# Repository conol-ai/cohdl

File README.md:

# CoHDL

CoHDL is the programming language that makes schematic (PCB) design AI-native — the way software became AI-native. AI generates and repairs hardware; the compiler is the oracle that grades it.

This is the **v2 ground-up implementation**, restarted 2026-07-13 from the redesigned language specification. The central thesis of the redesign: **strictness buys expressiveness** — push correctness into the type system wherever a mistake is structural (wrong units, unresolved pins, unsatisfied trait bounds), and reserve DRC only for genuinely emergent, whole-graph checks (net voltage, driver conflicts).

The previous implementation lives on the [`legacy`](https://github.com/conol-ai/cohdl/tree/legacy) branch. It is not being fixed; this is a fresh build informed by its lessons.

## Design repository

The source of truth for the language design is the Coherent Design Repository on conol.ai:
<https://conol.ai/share/note/tqrnb5h4l0dv8c14dkd17h4l>

A snapshot (taken 2026-07-13) is committed under [`docs/design/`](docs/design/). Key documents:

- [MVP Definition](docs/design/09-mvp-definition.md) — the scope line, demo scenario, and exit criteria this repository was built toward
- [Language Specification](docs/design/10-language-specification.md) — the compiled statement of what the language is (Accepted RFCs only)
- RFC-001…RFC-007 — the seven Accepted P0 RFCs: units-as-types, pin connection-obligation typing, trait satisfaction at impl time, DRC/type-system reclassification, collision-free designator allocation, nested fn call semantics, generics-over-specs
- RFC-008…RFC-018 — the post-MVP Accepted RFCs (compiler-implemented, with named open gaps recorded in [`docs/compliance-report.md`](docs/compliance-report.md) — notably RFC-016/017 on-disk dependency loading is not yet built, and RFC-014/015 real-client/partner acceptance passes remain open): structural variants, `cohdl fmt`, `cohdl check --json`, the formal error-code registry, `#[intent]` annotations, layout constraints, the LSP server (`cohdl lsp`, [`docs/lsp.md`](docs/lsp.md)), the IPC-2581 handoff document (`build --emit ipc2581`, [`docs/ipc2581.md`](docs/ipc2581.md)), the module system, the library registry, the pad/footprint format (`pad`/`footprint` geometry → `.kicad_mod` + IPC-2581 pins), and a real VS Code extension (`editors/vscode/`, packaging `cohdl lsp` with a TextMate grammar — RFC-019)

## MVP (v0.1) scope

The smallest slice of the spec that proves the thesis end-to-end:

1. **Parser** — traits, devices, free-standing `impl`, `fn` declarations/calls (nested), design bodies (`inst`, `net`, `nc`), the eleven unit-type literal forms
2. **Type checker** (the heart) — zero-coercion unit types, pin connection-obligation exhaustiveness, trait satisfaction with explicit mapping, generic resolution with trait-bound checking, nested fn expansion with cycle detection
3. **Residual DRC** — exactly four rules: voltage-exceed, polarity-mismatch, single-driver, multi-driver
4. **Designators** — collision-free allocator, `design.lock` with tombstones, `#[designator("…")]` overrides
5. **Codegen** — KiCad `.net` netlist + BOM CSV
6. **Minimal std library** — only the universal traits every component package needs
7. **Repair harness** — generate → check → repair loop driving an LLM against the compiler's diagnostics

The proof: an AI writes a board from a plain-language spec, the type checker catches its structural mistakes as precise compile errors, the AI repairs them from those diagnostics, and the result is a real, importable KiCad netlist with an honest BOM.

## Status

All MVP exit criteria are met, and all nineteen Accepted RFC areas (RFC-001…019) have implementation work with conformance suites. That is deliberately not a claim of full accepted-text compliance: requirements that are incomplete (e.g. RFC-014's real-editor acceptance pass and RFC-015's real-partner/Quilter import pass — both open), deliberately deviating (e.g. the E9xx code assignment, D003's role-aware reading, RFC-015's constraint mapping riding vendor extensions rather than native IPC semantics), or unrepresentable pending note-side amendments (e.g. RFC-013's E1005) are each recorded with rationale in the ledger, [`docs/compliance-report.md`](docs/compliance-report.md). Tested (`cargo test` — [`tests/exit_criteria.rs`](tests/exit_criteria.rs) maps 1:1 to the MVP checklist; each post-MVP RFC has its own conformance suite under `tests/`). The demo loop has run end-to-end: see [`docs/demo/`](docs/demo/) for transcripts (including a genuine E701 unresolved-required-pin catch + repair) and the emitted netlist/BOM. RFC/decision-record accuracy was audited claim-by-claim: [`docs/compliance-report.md`](docs/compliance-report.md). The KiCad checkpoint has been executed with real KiCad (pcbnew imported the netlist, resolved all footprints and pads; board + render in `docs/demo/`).

## Install

One line (macOS and Linux; installs to `~/.cohdl/bin`):

```sh
curl -fsSL https://raw.githubusercontent.com/conol-ai/cohdl/main/install.sh | sh
```

Prebuilt binaries (and their `sha256sums.txt`) are attached to every
[`vX.Y.Z` release](https://github.com/conol-ai/cohdl/releases); Windows users
download `cohdl-vX.Y.Z-x86_64-pc-windows-msvc.tar.gz` by hand. An installed
binary updates itself with `cohdl self-update` (`--check` reports without
installing). Building from source stays `cargo build` (toolchain pinned by
`rust-toolchain.toml`).

## Using it

```sh
cargo run -- check examples/sf32-miniboard       # SF32 miniboard: SiFli BLE eval board
cargo run -- build examples/rpi-pico2            # + designators, parts, KiCad .net + BOM CSV
cargo run -- check examples/rpi-pico2 --json     # structured diagnostics (RFC-010)
cargo run -- build examples/rpi-pico2 --emit ipc2581  # + IPC-2581 handoff document (RFC-015)
cargo run -- build examples/rpi-pico2 --emit kicad_pcb # + a native KiCad 10 board file — no KiCad needed
cargo run -- build examples/rpi-pico2 --emit easyeda   # + an EasyEDA / LCEDA Pro netlist (.enet)
cargo run -- build examples/rpi-pico2 --supplier acme   # + supplier BOM/map/CPL (RFC-034)
cargo run -- fmt lib --check                     # canonical-form gate (RFC-009)
cargo run -- lsp                                 # LSP server on stdio (RFC-014, docs/lsp.md)
cargo run -- search TPS59650                     # search registry packages + public parts
cargo run -- search TPS59650 --json              # the same bounded results as JSON
python3 harness/repair_loop.py                   # the generate → check → repair demo
```

Physical builds of placed designs also write `out/<name>-cpl.csv`, the
supplier-neutral five-column placement CSV. Under RFC-034,
repeatable `--supplier ID` selects each instance's own primary or eligible
alternate binding and writes `out/<name>-<ID>-bom.csv`,
`out/<name>-<ID>-map.json`, and (for physical builds)
`out/<name>-<ID>-cpl.csv`. The map preserves the selected entry identity and
placement transform; `tools/smt_pos.py --map` can apply it to the emitted
KiCad board. `--logical-only` remains a logical-artifact boundary: it emits
no neutral or supplier CPL, even when `--supplier` is present. Supplier BOM
and map remain available in that mode. Repeatable build option
`--bottom-rotation ID=VALUE` selects the bottom-side angle convention (`kicad`
or `mirrored`) for a supplier CPL; IDs must also be selected by `--supplier`
and default to `kicad`. Schema-2 maps record the convention actually used,
including in logical-only builds, and `tools/smt_pos.py --map` applies the same
rule (schema-1 maps retain `kicad` compatibility).

`cohdl search QUERY [--json]` is read-only discovery: it needs no project and
no registry login. Queries are trimmed, must contain at least three Unicode
scalar values, may be at most 128 UTF-8 bytes, and may not contain control
characters. Results identify the owning package and exact most-recently-
published version as well as importable public part paths and matching primary
or alternate manufacturer/MPN data; a valid query with no matches still exits
successfully. Use the standard option terminator when a literal query starts
with a hyphen, for example `cohdl search -- -12V`. “Most recently published”
is publication chronology, not the greatest semantic version chosen by an
unversioned `cohdl add`/`cohdl update`.
The package and part result families are bounded independently; each exposes
`has_more` when truncated and never a total count. Human output separates the
two families, while `--json` returns the same rows as one discovery document.
For rollout, owners of existing packages backfill the current searchable
version once with `cohdl docs --publish`; this does not change its tar or hash.

`std` is a core-traits-only prelude; it carries no devices, parts, pads, or
footprints. Shipped component packages include `passive`, `connectors`, `usb`,
`esd`, `diode`, `flash`, `ldo`, `led`, `mic`, `mosfet`, `osc`, and
manufacturer packages for Espressif, Raspberry Pi, Richtek, ST, and TI.
Projects pin every package they use to an exact version under
`[dependencies]`; see [`lib/README.md`](lib/README.md) for the complete
namespace map.

Two reference designs live in `examples/`: Raspberry Pi **Pico 2** and the
**SF32 miniboard**. (The **OpenMicro** macropad — the wired STM32F072 v1 and
its wireless SF32LB52 successor v2 — graduated to its own repository,
`openmicrokbd`, which carries the whole product: hardware source, firmware,
host app, and fab releases under `hw/v1/` and `hw/v2/`.)

An **AI voice robot-dog mainboard** is in progress and not yet in the tree; its
exit-criteria test is checked in but ignored until the example lands. It
combines an ESP32-S3-N8R2, stereo I2S microphones,
isolated speaker playback, a translated 1.8 V IMU domain, USB-C, a protected
default-off 7 A actuator rail, and eight 5 V servo PWM channels. Keyed 4/6-pin
Micro-Fit harnesses prevent the BEC input from being interchanged with a leg.

### Build artifacts

`cohdl build` writes to `out/` (or `--out-dir`): the KiCad netlist (`<name>.net`), the BOM (`<name>-bom.csv`), the designator lock (`design.lock` in the project root), a `.kicad_mod` per pad-bearing footprint under `out/footprints/` (RFC-018), and — only when the design declares layout metadata — the layout-constraint artifact `<name>-layout.json` (schema: [`docs/layout-json.md`](docs/layout-json.md)). With `--emit ipc2581` it additionally writes the IPC-2581B1 handoff document `<name>.xml` (RFC-015; [`docs/ipc2581.md`](docs/ipc2581.md)), with `--emit kicad_pcb` a native KiCad 10 board file `<name>.kicad_pcb` — placements, net-bound footprints, and the board outline, with no KiCad installation involved ([`docs/kicad_pcb.md`](docs/kicad_pcb.md)), and with `--emit easyeda` an EasyEDA / LCEDA Pro netlist `<name>.enet` for **File → Import → Netlist** ([`docs/easyeda.md`](docs/easyeda.md)); the flags compose. Stale layout/IPC/board artifacts are removed when their source data is gone (the IPC document only if CoHDL wrote it — its completeness marker establishes ownership).

### Looking at a design

A checked design can be read back as an interactive schematic-style board —
every instance, net and pin the compiler resolved, searchable and traceable,
with datasheets and to-scale footprint previews in a side panel. It is a
read-only projection: the `.cohdl` source stays the only thing that defines
the circuit.

On macOS, download the signed, notarized app from the latest
[`explorer-v*` release](https://github.com/conol-ai/cohdl/releases?q=explorer&expanded=true)
(mount the DMG, drag to Applications, pick a project). Or run it from source:

```sh
cd explorer/web && npm install && npm run build   # once
cd ../extractor
COHDL_LIB=../../lib cargo run --release -- ../../examples/rpi-pico2 \
    --serve --dist ../web/dist --port 5199        # http://127.0.0.1:5199/
```

Editing any source file re-extracts and refreshes the page within ~500 ms; a
source that fails to compile keeps the last good view and shows the
diagnostics. Extraction, layout and wire routing are deterministic code — the
same source always draws the same board. An agent's only input is the
partition file `explorer/views/<Design>.view.json`, which names the page tabs
and the region each part belongs to; the contract for writing one is
[`explorer/skills/view-gen/SKILL.md`](explorer/skills/view-gen/SKILL.md).
See [`explorer/README.md`](explorer/README.md).

### Exit codes

`0` = clean (warnings and a valid no-match search are allowed); `1` = the
accepted command failed (source errors, non-canonical `fmt --check`, or an E1204
search registry/protocol failure); `2` = invocation-level failure (bad flags,
an invalid search query, missing project, design selection, nothing to build);
`3` = `cohdl suppliers` found an `unknown` or `mismatched` audited binding
(out-of-stock, unbound, and unlisted suppliers do not change the exit code).
Human diagnostics use stderr. A successful `search --json` emits its discovery
document on stdout, and an E1204 failure in that mode emits the existing
diagnostic JSON there; bad invocations remain prose-only on stderr. See the
formal [`docs/error-codes.md`](docs/error-codes.md) registry. Note: RFC-010's
text reserves stderr prose for pre-collection failures, so classifying
post-collection selection failures this way is a documented deviation pending
a note-side amendment (or a v2 schema envelope).

## License

MIT — see [`LICENSE`](LICENSE). This covers the compiler crate, the libraries
under `lib/`, the reference designs in `examples/`, the registry
server in `registry/`, the VS Code extension in `editors/vscode/`, and the
tooling in `tools/` and `harness/`.

Third-party material is not covered by that grant: the manufacturer documents
under `lib/*/docs/` keep their owners' terms, KiCad-derived footprints are
CC-BY-SA-4.0 as each such package records in its manifest and license files, and the supplier
catalog facts and assembly-preview captures under `tools/sourcing_data/` are
described in [`tools/sourcing_data/NOTICE.md`](tools/sourcing_data/NOTICE.md).

Every package published to registry.cohdl.org must declare its own
`[package] license`; every package shipped under `lib/` declares `MIT`.

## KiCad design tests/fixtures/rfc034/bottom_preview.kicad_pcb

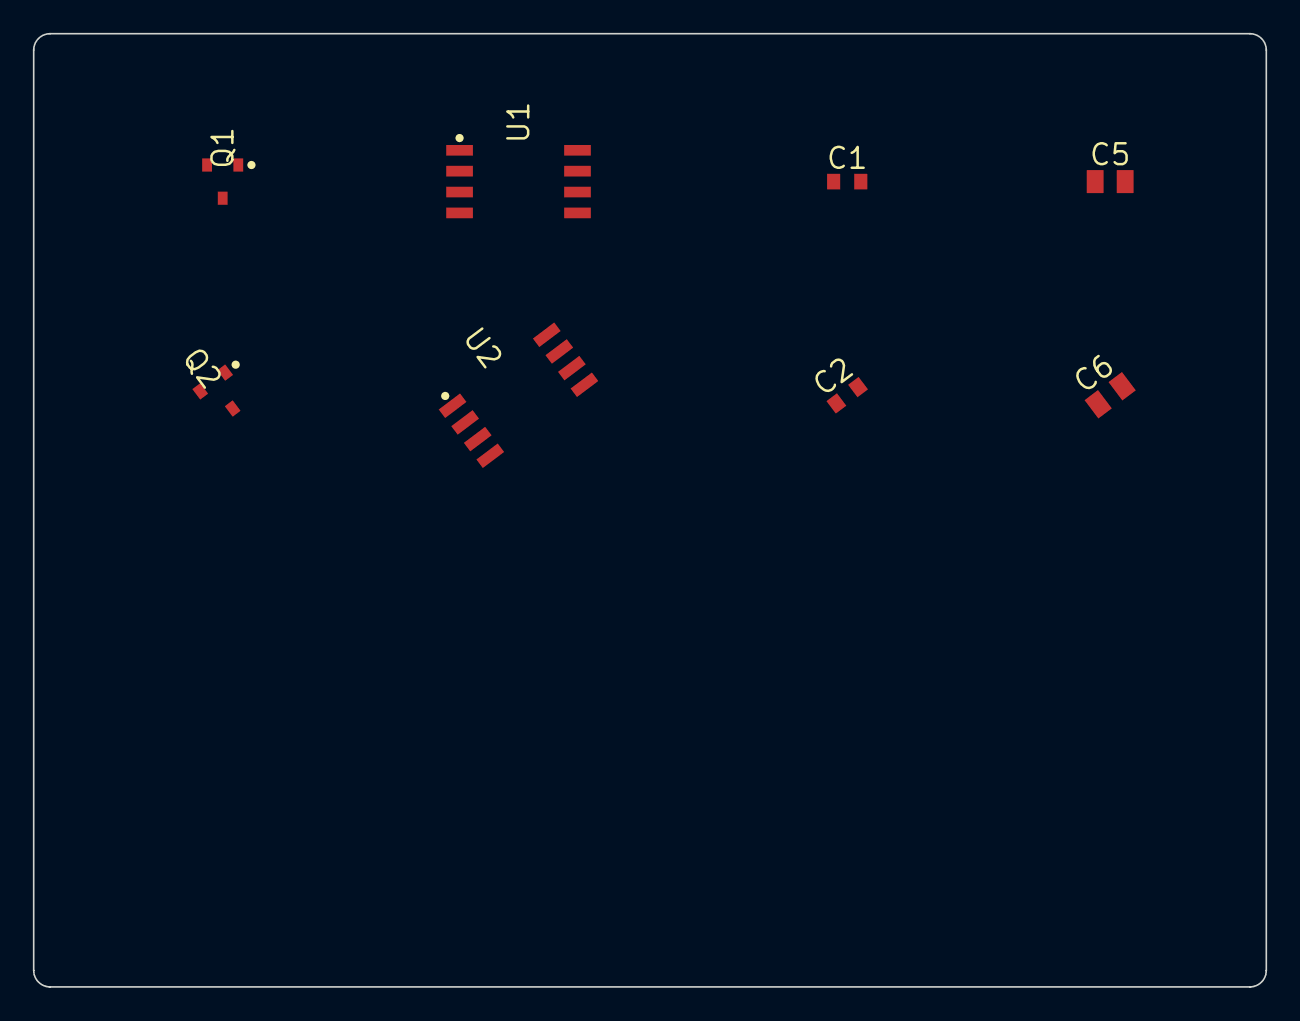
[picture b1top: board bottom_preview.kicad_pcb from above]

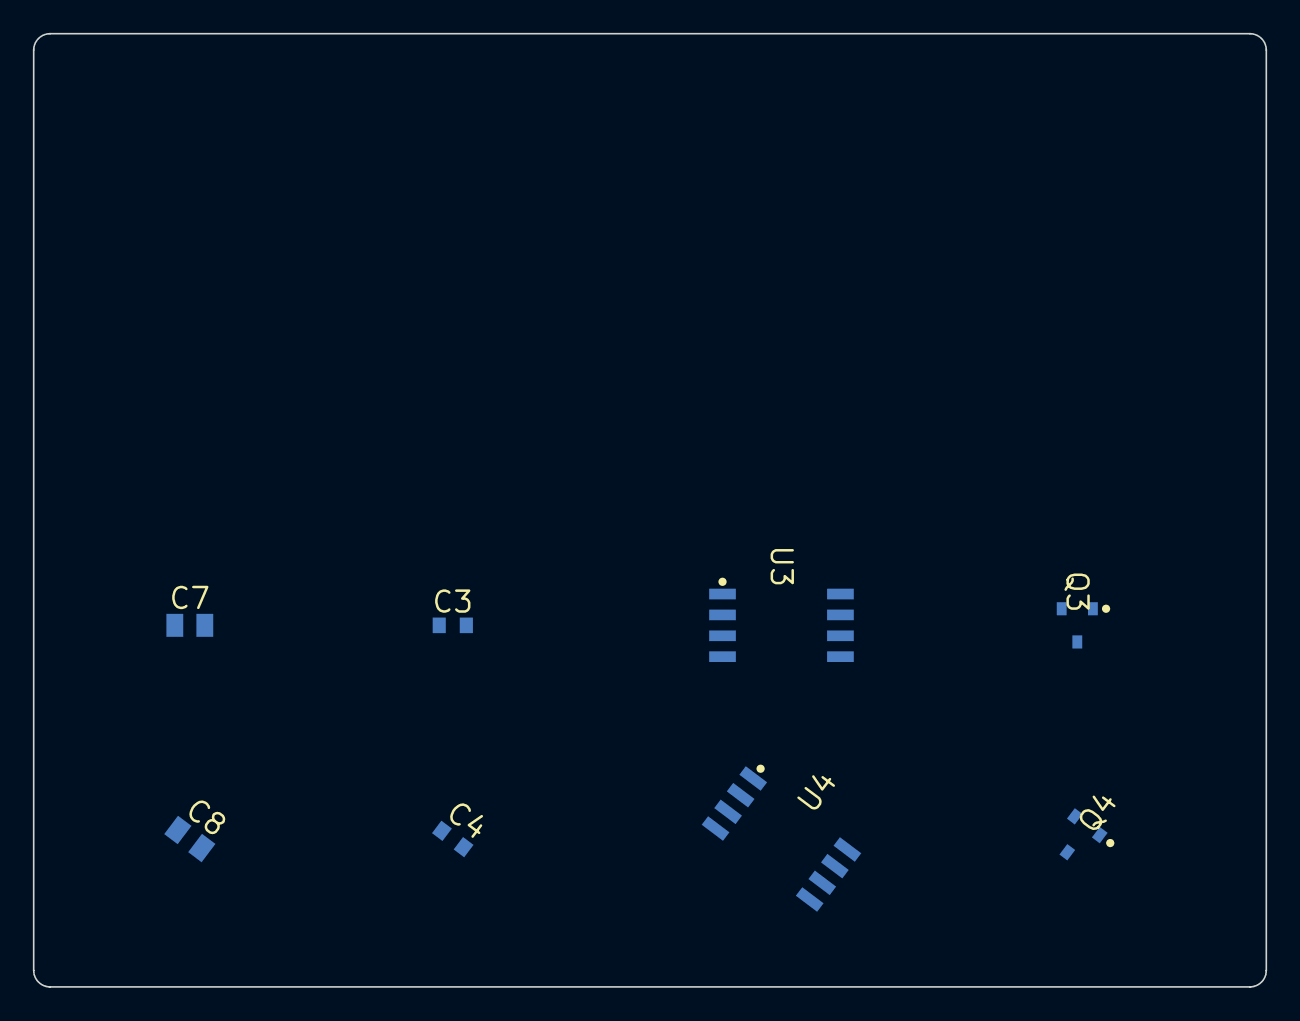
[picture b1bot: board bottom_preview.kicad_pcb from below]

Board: 2 copper layers, 75.0 x 58.0 mm, 16 parts (8 on the bottom side), 2 nets, no tracks yet.

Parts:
C1, C2, C3, C4: 27pF; passive-CHIP_0603
C5, C6, C7, C8: 15pF; passive-CHIP_0805
Q1, Q2, Q3, Q4: NPN_SOT23_BEC; transistor-FP_JSCJ_SOT23
U1, U2, U3, U4: W25Q128JV; soic-SOIC8P127X790X216N

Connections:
GND: C1.2, C2.2, C3.2, C4.2, C5.2, C6.2, C7.2, C8.2, Q1.2, Q2.2, Q3.2, Q4.2, U1.4, U2.4, U3.4, U4.4
V3V3: C1.1, C2.1, C3.1, C4.1, C5.1, C6.1, C7.1, C8.1, Q1.1, Q1.3, Q2.1, Q2.3, Q3.1, Q3.3, Q4.1, Q4.3, U1.8, U2.8, U3.8, U4.8

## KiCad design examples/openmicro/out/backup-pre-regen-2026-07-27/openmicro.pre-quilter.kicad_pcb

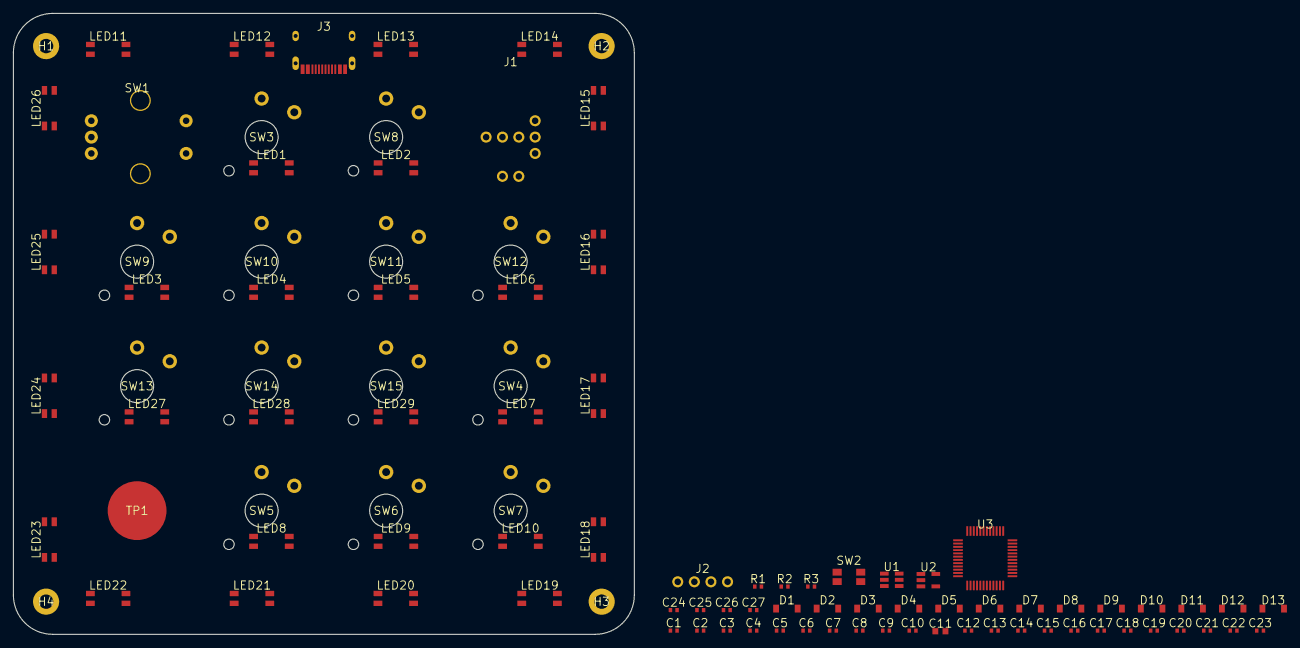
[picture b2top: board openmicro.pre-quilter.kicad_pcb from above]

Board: 2 copper layers, 95.0 x 95.0 mm, 98 parts (0 on the bottom side), 70 nets, no tracks yet.

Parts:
C1, C2, C3, C4, C5, C6, C7, C8, C9, C10, C13, C14, C15, C16, C17, C18, C19, C20, C21, C22, C23, C24, C25, C26, C27: 100nF; std-CHIP_0402
C11: 4.7uF; std-CHIP_0603
C12: 1uF; std-CHIP_0402
D1, D2, D3, D4, D5, D6, D7, D8, D9, D10, D11, D12, D13: Diode_1N4148; openmicro-FP_D_SOD_123
H1, H2, H3, H4: MountingHole; openmicro-FP_MountingHole_M2
J1: ThumbPointer; openmicro-FP_Joystick_RKJXV
J2: SWD_Header; openmicro-FP_Header_1x4
J3: USB_C_Receptacle_2_0; std-FP_USB_C_Receptacle_HRO_TYPE_C_31_M_12
LED1, LED2, LED3, LED4, LED5, LED6, LED7, LED8, LED9, LED10, LED11, LED12, LED13, LED14, LED15, LED16, LED17, LED18, LED19, LED20, LED21, LED22, LED23, LED24, LED25, LED26, LED27, LED28, LED29: SK6812; openmicro-FP_LED_SK6812MINI_E
R1: 10kohm; std-CHIP_0402
R2, R3: 5.1kohm; std-CHIP_0402
SW1: RotaryEC11; openmicro-FP_Encoder_EC11
SW2: ResetSwitch; openmicro-FP_SW_Reset
SW3, SW4, SW5, SW6, SW7, SW8, SW9, SW10, SW11, SW12, SW13, SW14, SW15: KeySwitch; openmicro-FP_SW_Choc_V2
TP1: CapTouchPad; openmicro-FP_TouchPad
U1: USBLC6; openmicro-FP_SOT_23_6
U2: AP2112K_3V3; std-SOT5P95X290X160N
U3: STM32F072CBT6; openmicro-QFP50P900X900X160_48N

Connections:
BOOT0: R1.1, U3.44
CC1: J3.A5, R2.1
CC2: J3.B5, R3.1
COL0: D1.1, D5.1, D9.1, D13.1, U3.25
COL1: D2.1, D6.1, D10.1, U3.26
COL2: D3.1, D7.1, D11.1, U3.27
COL3: D4.1, D8.1, D12.1, U3.28
ENC_A: SW1.1, U3.29
ENC_B: SW1.3, U3.30
ENC_SW: SW1.4, U3.31
GND: C1.2, C2.2, C3.2, C4.2, C5.2, C6.2, C7.2, C8.2, C9.2, C10.2, C11.2, C12.2, C13.2, C14.2, C15.2, C16.2, C17.2, C18.2, C19.2, C20.2, C21.2, C22.2, C23.2, C24.2, C25.2, C26.2, C27.2, H1.1, H2.1, H3.1, H4.1, J1.1, J1.4, J1.8, J2.3, J3.A1, J3.A12, J3.B1, J3.B12, J3.SH1, J3.SH2, J3.SH3, J3.SH4, LED1.3, LED2.3, LED3.3, LED4.3, LED5.3, LED6.3, LED7.3, LED8.3, LED9.3, LED10.3, LED11.3, LED12.3, LED13.3, LED14.3, LED15.3, LED16.3, LED17.3, LED18.3, LED19.3, LED20.3, LED21.3, LED22.3, LED23.3, LED24.3, LED25.3, LED26.3, LED27.3, LED28.3, LED29.3, R1.2, R2.2, R3.2, SW1.2, SW1.5, SW1.6, SW1.7, SW2.3, SW2.4, U1.2, U2.2, U3.8, U3.23, U3.35, U3.47
JOY_SW: J1.7, U3.12
JOY_X: J1.2, U3.10
JOY_Y: J1.5, U3.11
KEY1: D1.2, SW3.2
KEY2: D6.2, SW8.2
KEY3: D7.2, SW9.2
KEY4: D8.2, SW10.2
KEY5: D9.2, SW11.2
KEY6: D10.2, SW12.2
KEY7: D11.2, SW13.2
KEY8: D12.2, SW14.2
KEY9: D13.2, SW15.2
KEY10: D2.2, SW4.2
KEY11: D3.2, SW5.2
KEY12: D4.2, SW6.2
KEY13: D5.2, SW7.2
LED_D0: LED1.4, U3.41
LED_D1: LED1.2, LED2.4
LED_D2: LED2.2, LED3.4
LED_D3: LED3.2, LED4.4
LED_D4: LED4.2, LED5.4
LED_D5: LED5.2, LED6.4
LED_D6: LED6.2, LED27.4
LED_D7: LED27.2, LED28.4
LED_D8: LED28.2, LED29.4
LED_D9: LED7.4, LED29.2
LED_D10: LED7.2, LED8.4
LED_D11: LED8.2, LED9.4
LED_D12: LED9.2, LED10.4
NRST: SW2.1, SW2.2, U3.7
ROW0: SW3.1, SW8.1, SW9.1, SW10.1, U3.18
ROW1: SW11.1, SW12.1, SW13.1, SW14.1, U3.19
ROW2: SW4.1, SW5.1, SW6.1, SW15.1, U3.20
ROW3: SW7.1, U3.21
SWCLK: J2.2, U3.37
SWDIO: J2.1, U3.34
TOUCH: TP1.1, U3.13
UG_D0: LED11.4, U3.40
UG_D1: LED11.2, LED12.4
UG_D2: LED12.2, LED13.4
UG_D3: LED13.2, LED14.4
UG_D4: LED14.2, LED15.4
UG_D5: LED15.2, LED16.4
UG_D6: LED16.2, LED17.4
UG_D7: LED17.2, LED18.4
UG_D8: LED18.2, LED19.4
UG_D9: LED19.2, LED20.4
UG_D10: LED20.2, LED21.4
UG_D11: LED21.2, LED22.4
UG_D12: LED22.2, LED23.4
UG_D13: LED23.2, LED24.4
UG_D14: LED24.2, LED25.4
UG_D15: LED25.2, LED26.4
USBC_DM: J3.A7, J3.B7, U1.3
USBC_DP: J3.A6, J3.B6, U1.1
USB_DM: U1.4, U3.32
USB_DP: U1.6, U3.33
V3V3: C1.1, C2.1, C3.1, C12.1, J1.3, J1.6, J2.4, U2.5, U3.1, U3.9, U3.24, U3.36, U3.48
VBUS: C4.1, C5.1, C6.1, C7.1, C8.1, C9.1, C10.1, C11.1, C13.1, C14.1, C15.1, C16.1, C17.1, C18.1, C19.1, C20.1, C21.1, C22.1, C23.1, C24.1, C25.1, C26.1, C27.1, J3.A4, J3.A9, J3.B4, J3.B9, LED1.1, LED2.1, LED3.1, LED4.1, LED5.1, LED6.1, LED7.1, LED8.1, LED9.1, LED10.1, LED11.1, LED12.1, LED13.1, LED14.1, LED15.1, LED16.1, LED17.1, LED18.1, LED19.1, LED20.1, LED21.1, LED22.1, LED23.1, LED24.1, LED25.1, LED26.1, LED27.1, LED28.1, LED29.1, U1.5, U2.1, U2.3

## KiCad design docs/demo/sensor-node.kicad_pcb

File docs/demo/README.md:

# MVP demo evidence

The acceptance test from the MVP Definition
(`docs/design/09-mvp-definition.md`): from a one-paragraph natural-language
spec — *"An ESP32-S3-based sensor node: USB-C power/data, one MEMS microphone,
one status LED, a 3.3V LDO regulator, standard decoupling"* — an LLM (no
fine-tuning, prompted only with the language reference) writes `.cohdl`
source; the compiler grades it; diagnostics are fed back verbatim; the loop
lands on a clean design that emits a real KiCad netlist + BOM.

Reproduce with `python3 harness/repair_loop.py` (see the harness README
header for backends).

## Runs (2026-07-13)

| Run | Model | Reference | Attempts | Caught & repaired |
|---|---|---|---|---|
| 1 | claude-opus-4-8 | full | 2 | E202 ×2 (unresolved name), D003 warning |
| 2 | claude-opus-4-8 | full | 1 | — clean first try |
| 3 | claude-opus-4-8 | full | 1 | — clean first try |
| 4 | claude-opus-4-8 | full, reworded spec | 1 | — clean first try |
| 5 | claude-opus-4-8 | lean (no design notes) | 1 | — clean first try |
| 6 | claude-opus-4-8 | lean, detailed spec | 2 | E202 (unresolved name) |
| 7 | claude-haiku-4-5 | lean | 1 | — clean first try |
| 8 | claude-opus-4-8 | lean, +custom tantalum device | 1 | — clean first try (wrote device + impl mapping + part correctly) |
| **9** | **claude-haiku-4-5** | **lean, +custom tantalum device** | **2** | **E701 — unresolved required pin, repaired** |

## The proof transcript

[`transcript-flagship-haiku-e701.md`](transcript-flagship-haiku-e701.md) is
the run the MVP's non-negotiable clause asks for. On attempt 1 the model left
the ESP32-S3's chip-enable pin unwired, and the **type checker** — not DRC —
caught it as a compile error naming the exact line:

```text
error[E701]: required pin `SensorNode::esp32.EN` is unresolved: add it to a `net` or explicitly mark it `nc`
 --> src/main.cohdl:20:5
   |
20 |     inst esp32: ESP32_S3_WROOM_1_N8
   |     ^^^^^^^^^^^^^^^^^^^^^^^^^^^^^^^
  :: std/soc.cohdl:13:9
   |
13 |         required EN: 3 [input]
   |         ---------------------- `EN` is declared `required` on device `ESP32_S3_WROOM_1` here
```

This is the exact mistake class (a forgotten wire) that v1 shipped silently
and that RFC-002 moved into the type system. The diagnostic was fed back
verbatim; attempt 2 wired EN through a 10k pull-up and landed clean —
[`sensor-node.net`](sensor-node.net) and
[`sensor-node-bom.csv`](sensor-node-bom.csv) are its emitted artifacts.

Two supplementary transcripts:

- [`transcript-opus-e202.md`](transcript-opus-e202.md) — a resolution-error
  catch + repair cycle (the model invented a v1-style bare net reference,
  which the MVP grammar deliberately dropped).
- [`transcript-opus-custom-device.md`](transcript-opus-custom-device.md) —
  the expressiveness half of the thesis: asked for a part the std library
  doesn't have, the model declared a polarized tantalum device, the explicit
  `impl TwoTerminal` pin mapping (`A: Anode, B: Cathode`), `impl Capacitor` +
  `impl Polarized`, and a part binding — all first try, all checked at the
  impl statements.

A note on difficulty: 6 of 9 runs were clean on the first attempt. The type
system's catches fire exactly when the model errs — with a complete language
reference in context, frontier models err rarely, which is the
AI-generatability half of the design working as intended (Constitution
priority #2). The failed attempts are what the compiler-as-oracle is for.

## KiCad checkpoint — executed

The import was driven through real KiCad (pcbnew 10.0.4, its own engine, via
`tools/kicad_checkpoint.py` — the same work File → Import Netlist performs):

- **All 14 footprints resolved from KiCad's official libraries**, every
  netlist pin matched a real footprint pad, designators verified unique.
- The resulting board is committed as
  [`sensor-node.kicad_pcb`](sensor-node.kicad_pcb) (open it directly in
  pcbnew — footprints placed, pad nets assigned, connectivity drawn), with a
  rendered [`sensor-node-board.pdf`](sensor-node-board.pdf) showing the
  components and net connectivity: USB-C → CC pulldowns, VBUS → LDO → 3.3V
  rail → decoupling bank + tantalum, ESP32 → I2S mic, EN pull-up, LED chain.

The checkpoint caught a real netlist-fidelity bug, exactly as intended: the
std USB-C device used combined pad names (`A1B12`, `S1`) that don't exist on
KiCad's official HRO footprint (separate `A1…B12` pads, shield `SH`). The std
device was corrected against the real footprint and everything regenerated.

To confirm by eye: open `sensor-node.kicad_pcb` in KiCad (or just the PDF),
and cross-check `sensor-node-bom.csv` — every line item carries a real MPN.

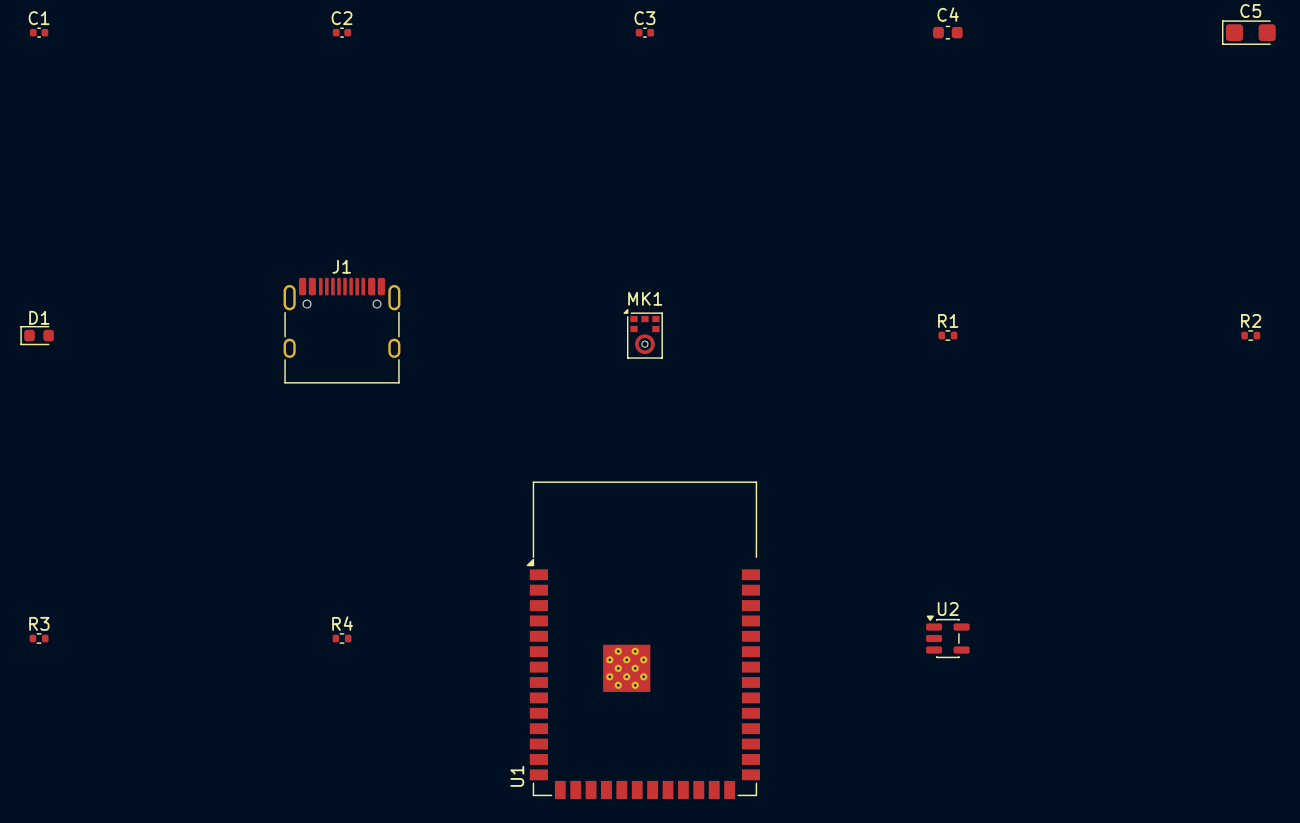
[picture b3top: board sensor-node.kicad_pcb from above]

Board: 2 copper layers, 14 parts (0 on the bottom side), 14 nets, no tracks yet.

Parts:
C1, C2, C3: 100nF; C_0402_1005Metric
C4: 10uF; C_0603_1608Metric
C5: 100uF; CP_EIA-3216-18_Kemet-A
D1: ChipLED; LED_0603_1608Metric
J1: USB_C_Receptacle_2_0; USB_C_Receptacle_HRO_TYPE-C-31-M-12
MK1: ICS43434; InvenSense_ICS-43434-6_3.5x2.65mm
R1: 1kohm; R_0402_1005Metric
R2, R3: 5.1kohm; R_0402_1005Metric
R4: 10kohm; R_0402_1005Metric
U1: ESP32_S3_WROOM_1; ESP32-S3-WROOM-1
U2: AP2112K_3V3; SOT-23-5

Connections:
CC1: J1.A5, R2.1
CC2: J1.B5, R3.1
DN: J1.A7, J1.B7, U1.13
DP: J1.A6, J1.B6, U1.14
EN: R4.2, U1.3
GND: C1.2, C2.2, C3.2, C4.2, C5.2, D1.1, J1.A1, J1.A12, J1.B1, J1.B12, J1.SH, MK1.6, R2.2, R3.2, U1.1, U1.40, U1.41, U2.2
LR: MK1.2, U1.15
SCK: MK1.3, U1.39
SD: MK1.4, U1.4
VBUS: J1.A4, J1.A9, J1.B4, J1.B9, U2.1
VDD: C1.1, C2.1, C3.1, C4.1, C5.1, MK1.5, R4.1, U1.2, U2.3, U2.5
WS: MK1.1, U1.38
__fn0_status_led::__net0: R1.1, U1.5
__fn0_status_led::__net1: D1.2, R1.2

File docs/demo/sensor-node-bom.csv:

RefDes,Value,MPN,Manufacturer,Qty
"U2","AP2112K_3V3","AP2112K-3.3TRG1","Diodes Inc",1
"C1,C2,C3","100nF","CL05B104KO5NNNC","Samsung",3
"C4","10uF","CL10A106KP8NNNC","Samsung",1
"U1","ESP32_S3_WROOM_1","ESP32-S3-WROOM-1-N8","Espressif",1
"MK1","ICS43434","ICS-43434","TDK InvenSense",1
"D1","ChipLED","LTST-C193KRKT-5A","Lite-On",1
"R4","10kohm","RC0402FR-0710KL","Yageo",1
"R1","1kohm","RC0402FR-071KL","Yageo",1
"R2,R3","5.1kohm","RC0402FR-075K1L","Yageo",2
"C5","100uF","T491A107K010AT","Kemet",1
"J1","USB_C_Receptacle_2_0","TYPE-C-31-M-12","HRO",1
